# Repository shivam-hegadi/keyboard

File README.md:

# Keyboard Build Log
 
This document outlines my process for designing and building my first custom mechanical keyboard from scratch, including PCB design, custom keycap design, and case engineering.
 
## Journal 1: Initial Concept
**Time: 1 hour 30 minutes** 
I decided to design a 65% keyboard with circular keycaps. My goal was to create a sleek design with resin keycaps and LEDs mounted behind the switches to provide underglow lighting.

## Journal 2: Layout Design
**Time: 2 hours**
 
I began designing the schematic in KiCAD but encountered difficulties visualizing where the keys should be positioned and determining appropriate key sizes. I discovered keyboard-layout-editor.com, which allowed me to create an accurate layout template before proceeding with the actual PCB design. This tool significantly improved my understanding of the final layout.

## Journal 3: Schematic Development
**Time: 1 hour 30 minutes**
 
I realized that the schematic does not need to be a perfectly accurate representation of the physical PCB layout. It only needs to show all electrical connections accurately. Once I understood this principle, I was able to progress more effectively with the wiring design.
 
## Journal 4: Switch Matrix Wiring
**Time: 2 hours**
 
I completed the wiring of all switches in a matrix configuration. I have not yet connected this to the Pi Pico microcontroller. I also need to research and integrate the two rotary encoders into the design. This step required significant research, and I learned a great deal about how keyboard matrix scanning works.

## Journal 5: Complete Schematic
**Time: 1 hour 30 minutes**
 
I finished wiring the complete schematic, including both rotary encoders. I added six stabilizers total, with two additional stabilizers included as spares in case they are needed during final assembly. The schematic is now complete and ready for PCB layout design.

## Journal 6: PCB Component Placement
**Time: 3 hours**
 
I placed all switches, the Pi Pico microcontroller, stabilizers, and rotary encoders on the PCB. I adjusted the spacing between switches multiple times to match my original design specifications. The next phase will involve routing all electrical traces.

## Journal 7: Trace Routing and Verification
**Time: 4 hours**
 
This was the most time-consuming phase of the project. I routed all traces and performed verification using KiCAD's DRC (Design Rule Check) checker. I had to ensure that no traces crossed and that all components maintained proper spacing. The design has been verified and is ready for manufacturing.

## Journal 8: Custom Silkscreen Design
**Time: 2 hours**
 
I added personalization to the PCB by designing a custom silkscreen on the front with my name and a full board design on the back. I discovered that silkscreen designs must be rendered in black for KiCAD to display them correctly on screen.

## Journal 9: Three-Dimensional Assembly
**Time: 2 hours 30 minutes**
 
I imported the PCB STEP file into Fusion 360 and began adding three-dimensional models of the switches and rotary encoders. The diodes and Pi Pico were already included in the STEP file because they had 3D models linked to their KiCAD footprints. Although manually placing each switch in its correct position was tedious, this process allowed me to visualize the final assembly.

## Journal 10: Plate Design
**Time: 1 hour**
 
I designed the plate using Fusion's 3D sketch feature to trace the keycap outlines. This approach proved to be effective and more straightforward than anticipated. I selected a bottom-mounted configuration for this keyboard design.

## Journal 11: Custom Keycap Design
**Time: 2 hours 30 minutes**
 
I completed the design of all custom keycaps using a circular profile with a loft feature. The longer keycaps, such as the shift and spacebar keys, presented challenges because the 3D sketch feature does not permit vertical movement of sketches. I had to redesign these sketches multiple times before achieving the desired result. I selected resin as the material for its translucent properties.

## Journal 12: Outer Case Design
**Time: 1 hour 30 minutes**
 
I designed the outer case with two separate pieces that sandwich the plate assembly in the middle, ensuring secure assembly. I selected wood as the case material because I plan to machine the case from wood stock that I currently have available.

## Final Render
 
I utilized my complimentary Autodesk Education cloud rendering credits to create a final visualization of the complete keyboard assembly.

## Total Hours

In total, I spent 25 Hours and 30 Minutes on this projects design phase. As this was my first time making a PCB, I had a big learning curve with Kicad, so it took a bit longer than expected. Helpful tools such as the Marbastlib in Kicad and 3D Sketch in Fusion helped a lot with saving time. I am excited to get my grant and order the PCB and parts!

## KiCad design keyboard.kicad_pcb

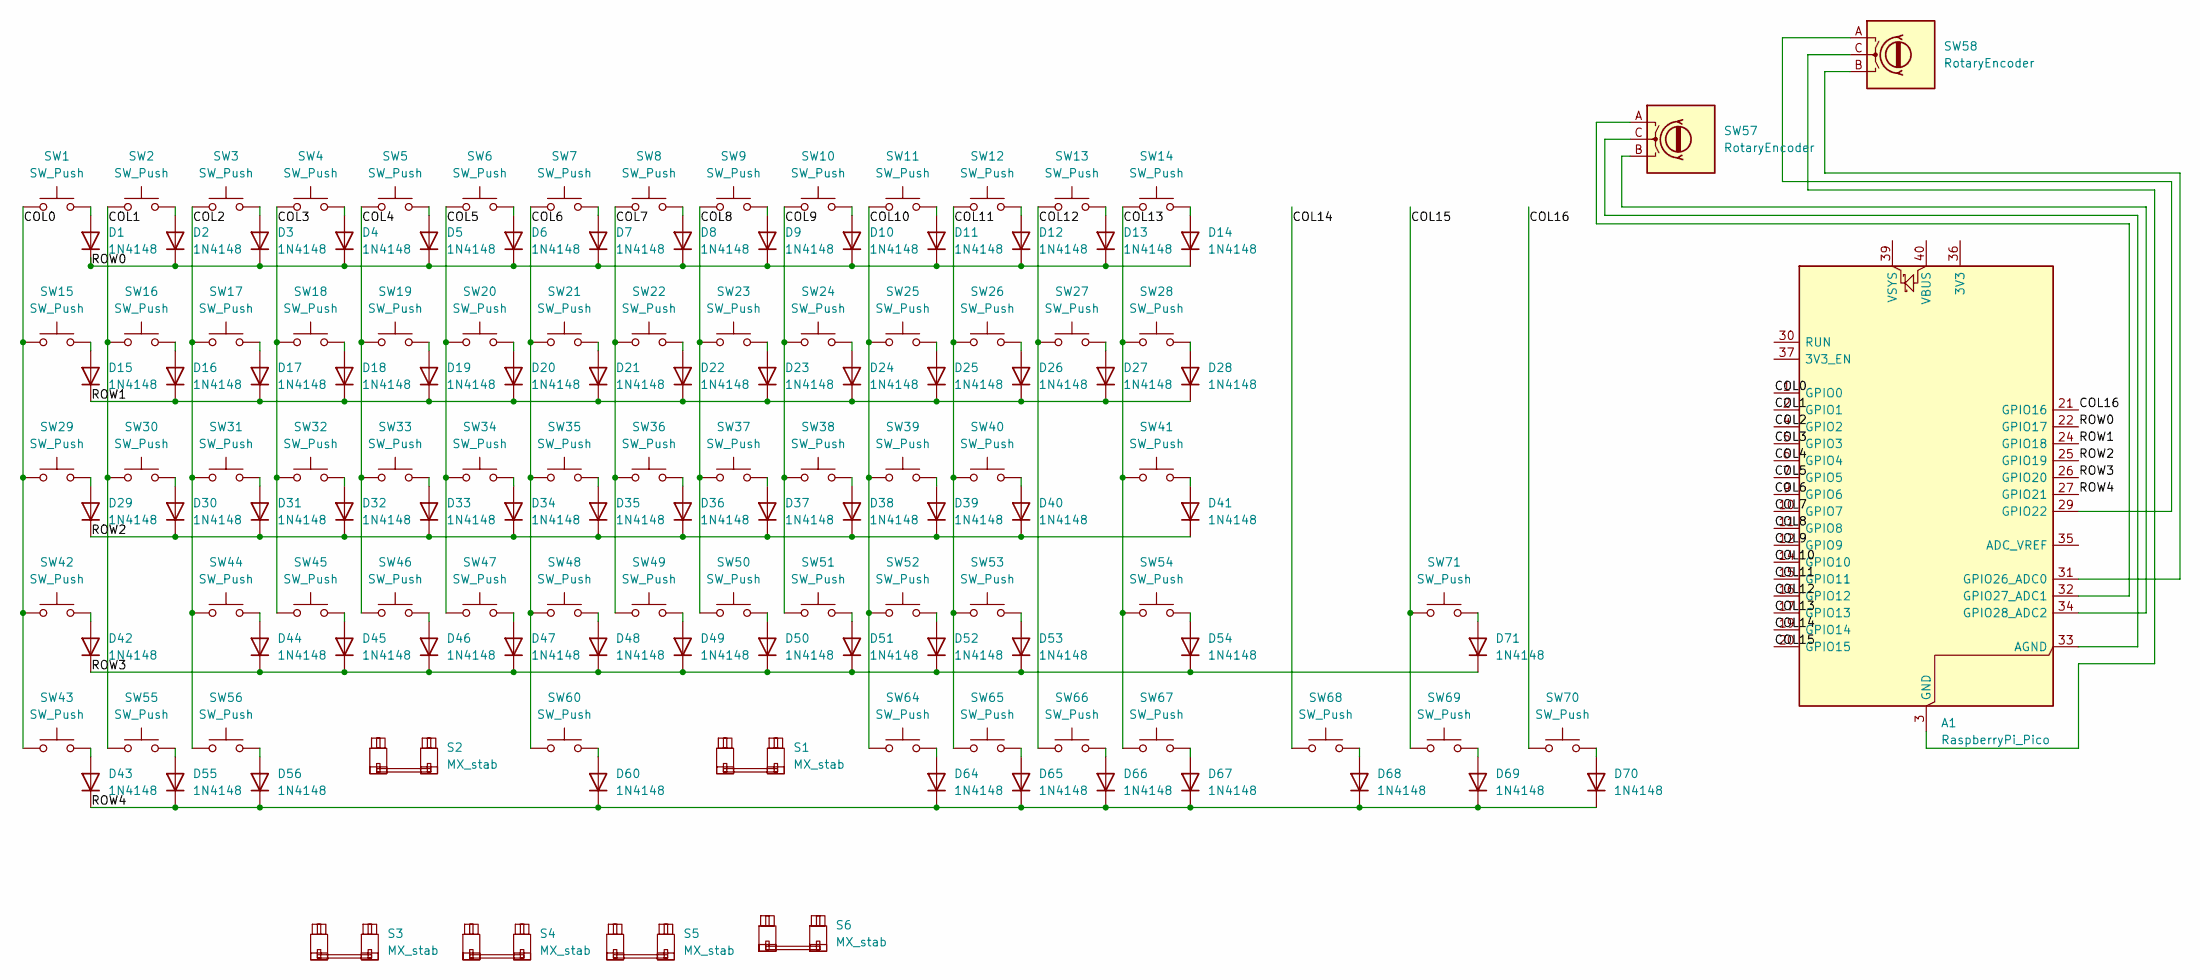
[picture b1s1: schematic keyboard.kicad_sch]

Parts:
A1: RaspberryPi_Pico; RaspberryPi_Pico_Common_THT
D1, D2, D3, D4, D5, D6, D7, D8, D9, D10, D11, D12, D13, D14, D15, D16, D17, D18, D19, D20, D21, D22, D23, D24, D25, D26, D27, D28, D29, D30, D31, D32, D33, D34, D35, D36, D37, D38, D39, D40, D41, D42, D43, D44, D45, D46, D47, D48, D49, D50, D51, D52, D53, D54, D55, D56, D60, D64, D65, D66, D67, D68, D69, D70, D71: 1N4148; D_DO-35_SOD27_P7.62mm_Horizontal
S1, S2, S3, S5, S6: MX_stab; STAB_MX_P_6.25u
S4: MX_stab; STAB_MX_2.25u
SW1, SW2, SW3, SW4, SW5, SW6, SW7, SW8, SW9, SW10, SW11, SW12, SW13, SW14, SW15, SW16, SW17, SW18, SW19, SW20, SW21, SW22, SW23, SW24, SW25, SW26, SW27, SW28, SW29, SW30, SW31, SW32, SW33, SW34, SW35, SW36, SW37, SW38, SW39, SW40, SW41, SW42, SW43, SW44, SW45, SW46, SW47, SW48, SW49, SW50, SW51, SW52, SW53, SW54, SW55, SW56, SW60, SW64, SW65, SW66, SW67, SW68, SW69, SW70, SW71: SW_Push; SW_MX_1u
SW57, SW58: RotaryEncoder; RotaryEncoder_Bourns_Horizontal_PEC09-2xxxF-Nxxxx

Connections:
/<NO NET>: A1.12 (GPIO9), SW10.1, SW24.1, SW38.1, SW51.1
/COL0: A1.1 (GPIO0), SW1.1, SW15.1, SW29.1, SW42.1, SW43.1
/COL1: A1.2 (GPIO1), SW2.1, SW16.1, SW30.1, SW55.1
/COL2: A1.4 (GPIO2), SW3.1, SW17.1, SW31.1, SW44.1, SW56.1
/COL3: A1.5 (GPIO3), SW4.1, SW18.1, SW32.1, SW45.1
/COL4: A1.6 (GPIO4), SW5.1, SW19.1, SW33.1, SW46.1
/COL5: A1.7 (GPIO5), SW6.1, SW20.1, SW34.1, SW47.1
/COL6: A1.9 (GPIO6), SW7.1, SW21.1, SW35.1, SW48.1, SW60.1
/COL7: A1.10 (GPIO7), SW8.1, SW22.1, SW36.1, SW49.1
/COL8: A1.11 (GPIO8), SW9.1, SW23.1, SW37.1, SW50.1
/COL10: A1.14 (GPIO10), SW11.1, SW25.1, SW39.1, SW52.1, SW64.1
/COL11: A1.15 (GPIO11), SW12.1, SW26.1, SW40.1, SW53.1, SW65.1
/COL12: A1.16 (GPIO12), SW13.1, SW27.1, SW66.1
/COL13: A1.17 (GPIO13), SW14.1, SW28.1, SW41.1, SW54.1, SW67.1
/COL14: A1.19 (GPIO14), SW68.1
/COL15: A1.20 (GPIO15), SW69.1, SW71.1
/COL16: A1.21 (GPIO16), SW70.1
/ROW0: A1.22 (GPIO17), D1.1 (K), D2.1 (K), D3.1 (K), D4.1 (K), D5.1 (K), D6.1 (K), D7.1 (K), D8.1 (K), D9.1 (K), D10.1 (K), D11.1 (K), D12.1 (K), D13.1 (K), D14.1 (K)
/ROW1: A1.24 (GPIO18), D15.1 (K), D16.1 (K), D17.1 (K), D18.1 (K), D19.1 (K), D20.1 (K), D21.1 (K), D22.1 (K), D23.1 (K), D24.1 (K), D25.1 (K), D26.1 (K), D27.1 (K), D28.1 (K)
/ROW2: A1.25 (GPIO19), D29.1 (K), D30.1 (K), D31.1 (K), D32.1 (K), D33.1 (K), D34.1 (K), D35.1 (K), D36.1 (K), D37.1 (K), D38.1 (K), D39.1 (K), D40.1 (K), D41.1 (K)
/ROW3: A1.26 (GPIO20), D42.1 (K), D44.1 (K), D45.1 (K), D46.1 (K), D47.1 (K), D48.1 (K), D49.1 (K), D50.1 (K), D51.1 (K), D52.1 (K), D53.1 (K), D54.1 (K), D71.1 (K)
/ROW4: A1.27 (GPIO21), D43.1 (K), D55.1 (K), D56.1 (K), D60.1 (K), D64.1 (K), D65.1 (K), D66.1 (K), D67.1 (K), D68.1 (K), D69.1 (K), D70.1 (K)
unnamed: A1.33 (AGND), SW57.C
unnamed: A1.3 (GND), A1.8 (GND), A1.13 (GND), A1.18 (GND), A1.23 (GND), A1.28 (GND), A1.38 (GND), SW58.C
unnamed: A1.29 (GPIO22), SW58.A
unnamed: A1.31 (GPIO26_ADC0), SW58.B
unnamed: A1.32 (GPIO27_ADC1), SW57.A
unnamed: A1.34 (GPIO28_ADC2), SW57.B
unnamed: D1.2 (A), SW1.2
unnamed: D2.2 (A), SW2.2
unnamed: D3.2 (A), SW3.2
unnamed: D4.2 (A), SW4.2
unnamed: D5.2 (A), SW5.2
unnamed: D6.2 (A), SW6.2
unnamed: D7.2 (A), SW7.2
unnamed: D8.2 (A), SW8.2
unnamed: D9.2 (A), SW9.2
unnamed: D10.2 (A), SW10.2
unnamed: D11.2 (A), SW11.2
unnamed: D12.2 (A), SW12.2
unnamed: D13.2 (A), SW13.2
unnamed: D14.2 (A), SW14.2
unnamed: D15.2 (A), SW15.2
unnamed: D16.2 (A), SW16.2
unnamed: D17.2 (A), SW17.2
unnamed: D18.2 (A), SW18.2
unnamed: D19.2 (A), SW19.2
unnamed: D20.2 (A), SW20.2
unnamed: D21.2 (A), SW21.2
unnamed: D22.2 (A), SW22.2
unnamed: D23.2 (A), SW23.2
unnamed: D24.2 (A), SW24.2
unnamed: D25.2 (A), SW25.2
unnamed: D26.2 (A), SW26.2
unnamed: D27.2 (A), SW27.2
unnamed: D28.2 (A), SW28.2
unnamed: D29.2 (A), SW29.2
unnamed: D30.2 (A), SW30.2
unnamed: D31.2 (A), SW31.2
unnamed: D32.2 (A), SW32.2
unnamed: D33.2 (A), SW33.2
unnamed: D34.2 (A), SW34.2
unnamed: D35.2 (A), SW35.2
unnamed: D36.2 (A), SW36.2
unnamed: D37.2 (A), SW37.2
unnamed: D38.2 (A), SW38.2
unnamed: D39.2 (A), SW39.2
unnamed: D40.2 (A), SW40.2
unnamed: D41.2 (A), SW41.2
unnamed: D42.2 (A), SW42.2
unnamed: D43.2 (A), SW43.2
unnamed: D44.2 (A), SW44.2
unnamed: D45.2 (A), SW45.2
unnamed: D46.2 (A), SW46.2
unnamed: D47.2 (A), SW47.2
unnamed: D48.2 (A), SW48.2
unnamed: D49.2 (A), SW49.2
unnamed: D50.2 (A), SW50.2
unnamed: D51.2 (A), SW51.2
unnamed: D52.2 (A), SW52.2
unnamed: D53.2 (A), SW53.2
unnamed: D54.2 (A), SW54.2
unnamed: D55.2 (A), SW55.2
unnamed: D56.2 (A), SW56.2
unnamed: D60.2 (A), SW60.2
unnamed: D64.2 (A), SW64.2
unnamed: D65.2 (A), SW65.2
unnamed: D66.2 (A), SW66.2
unnamed: D67.2 (A), SW67.2
unnamed: D68.2 (A), SW68.2
unnamed: D69.2 (A), SW69.2
unnamed: D70.2 (A), SW70.2
unnamed: D71.2 (A), SW71.2

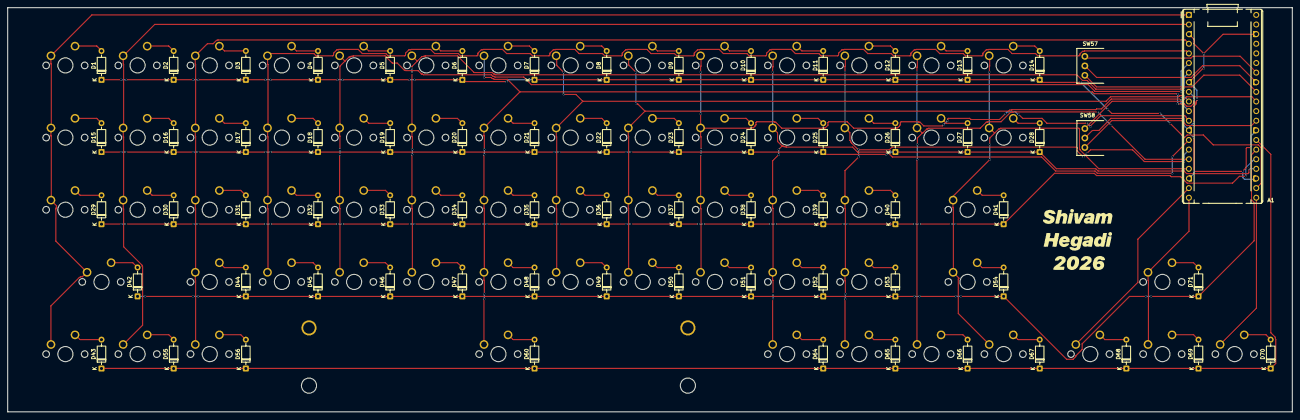
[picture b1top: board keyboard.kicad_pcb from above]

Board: 2 copper layers, 339.1 x 106.7 mm, 135 parts (0 on the bottom side), 93 nets.

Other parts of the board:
  : LOGO
